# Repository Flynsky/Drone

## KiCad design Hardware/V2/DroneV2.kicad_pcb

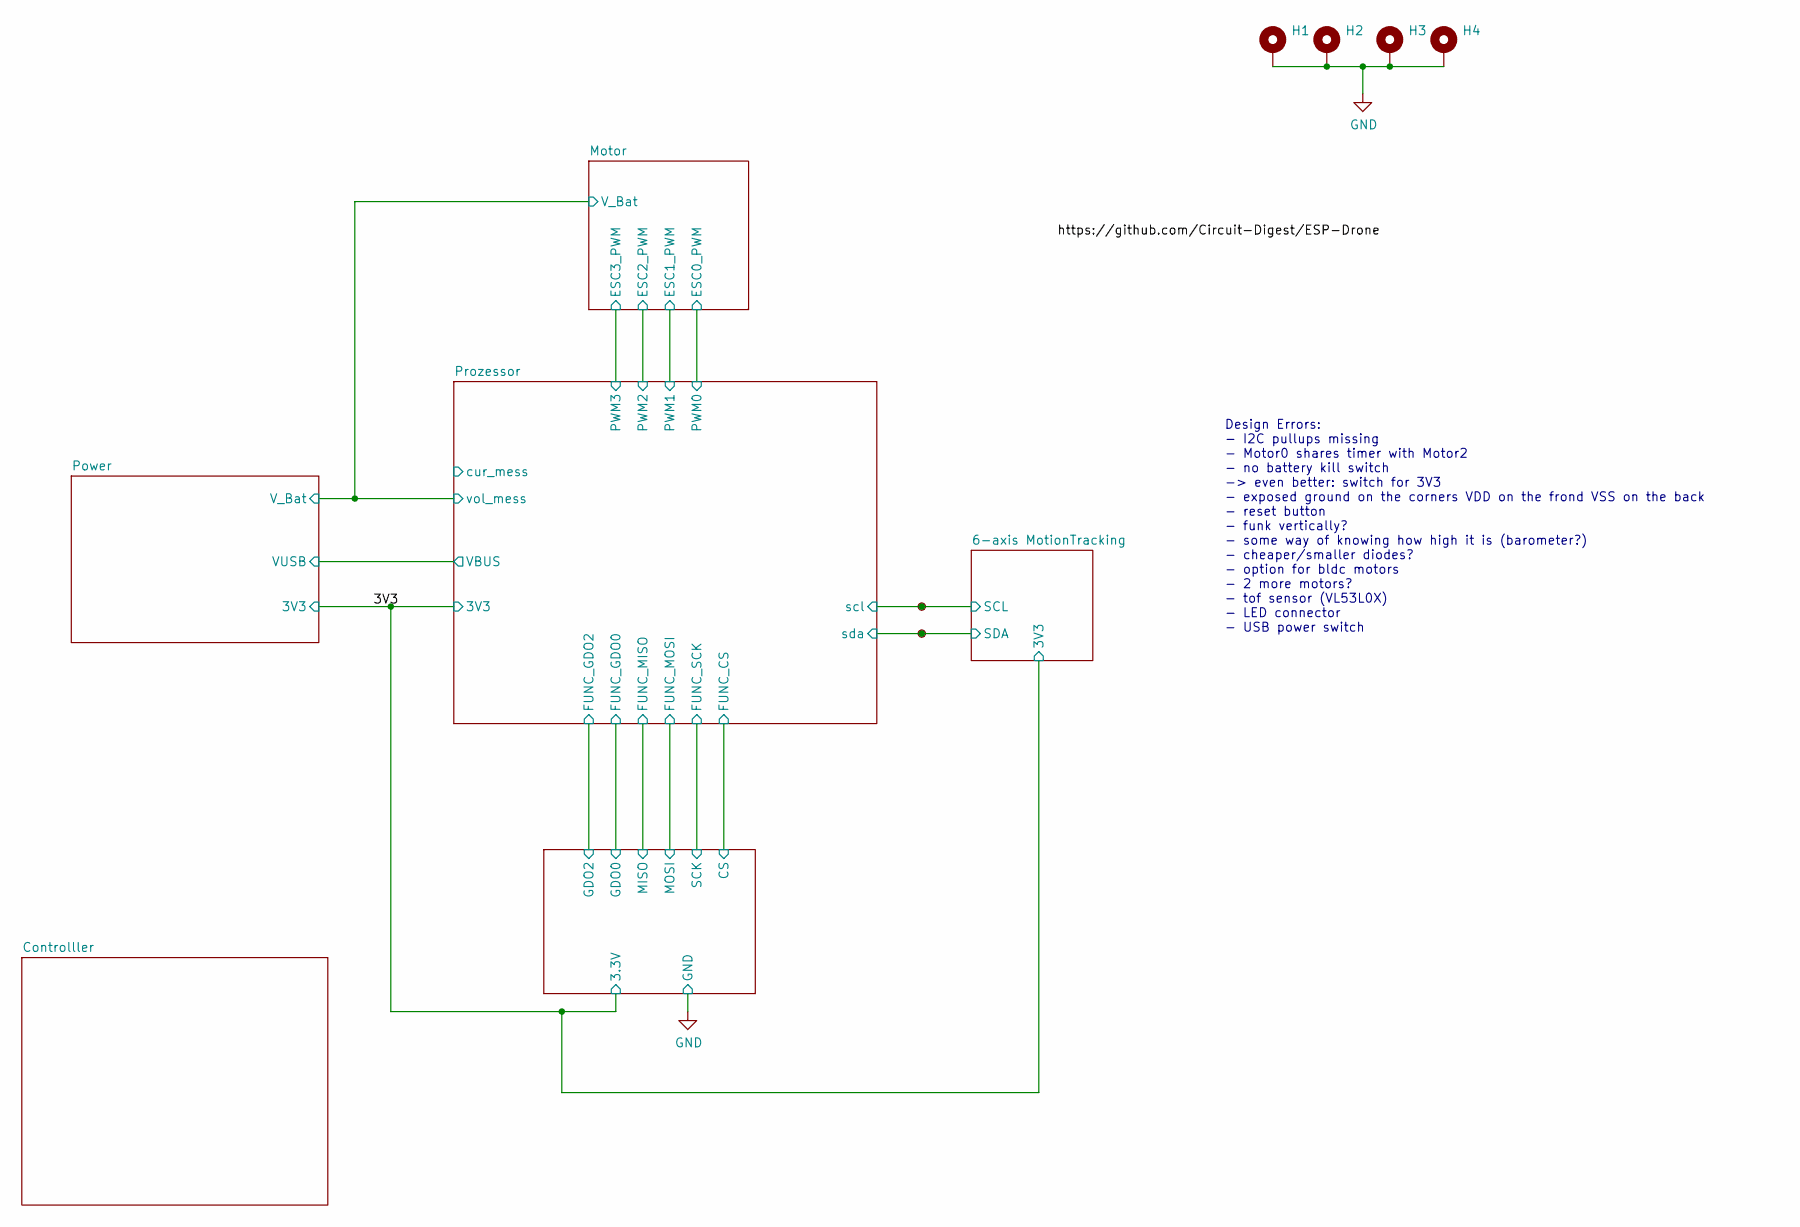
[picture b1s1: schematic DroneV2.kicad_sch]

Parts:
H1, H2, H3, H4: MountingHole_Pad; MountingHole_2.7mm_Pad_Via
TP1, TP2: TestPoint_Small; TestPoint_Pad_D1.0mm

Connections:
/6-axis MotionTracking/SCL: TP1.1; also elsewhere on the board
/6-axis MotionTracking/SDA: TP2.1; also elsewhere on the board
GND: H1.1, H2.1, H3.1, H4.1; also elsewhere on the board

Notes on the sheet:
Design Errors: - I2C pullups missing - Motor0 shares timer with Motor2 - no battery kill switch -> even better: switch for 3V3 - exposed ground on the corners VDD on the frond VSS on the back - reset button - funk vertically? - some way of knowing how high it is (barometer?) - cheaper/smaller diode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

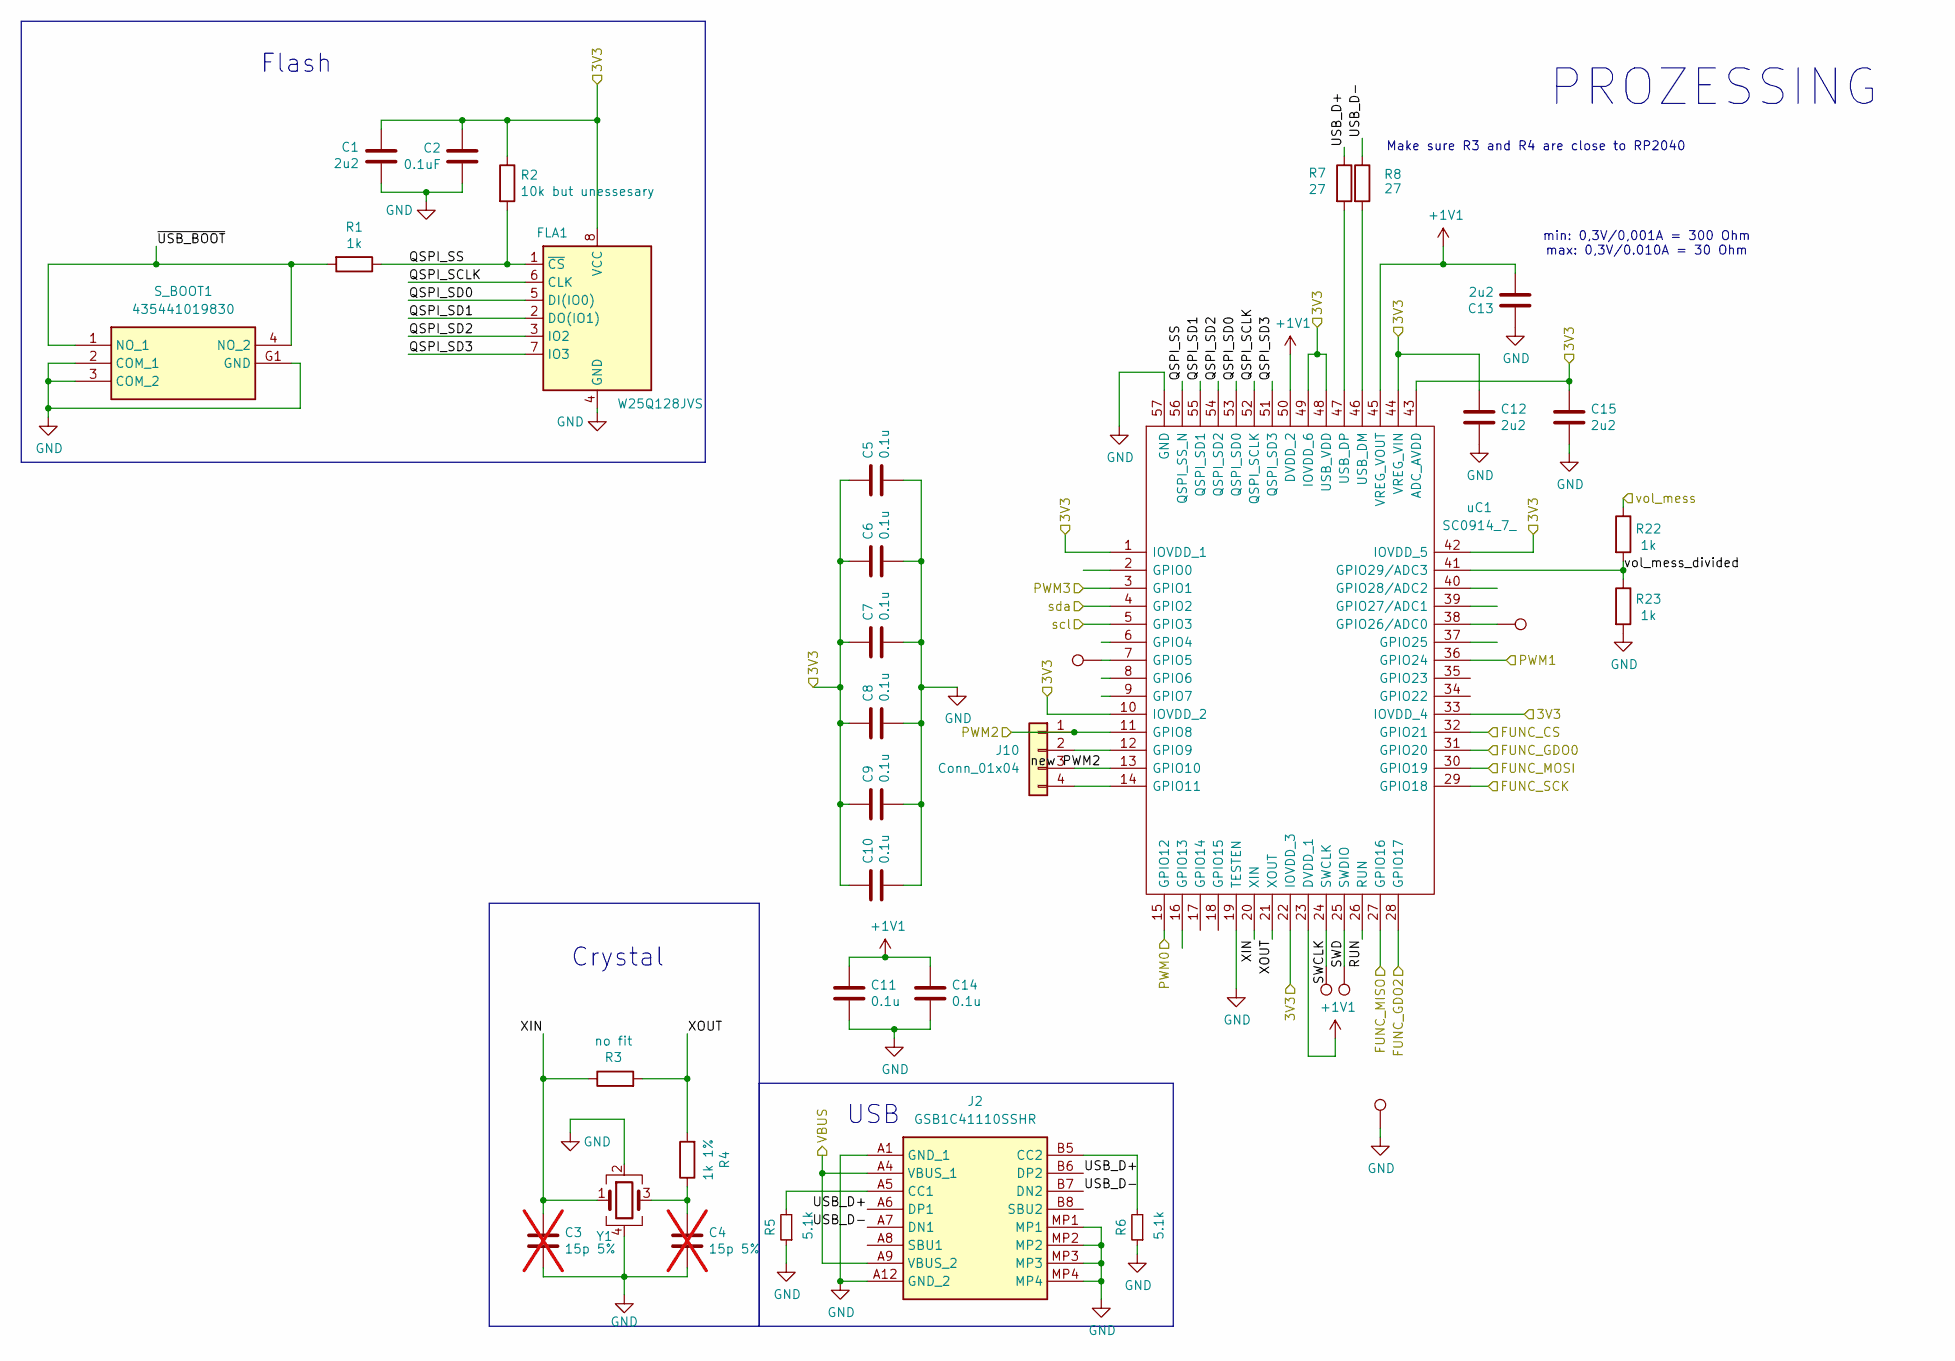
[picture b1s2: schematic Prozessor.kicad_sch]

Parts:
C1, C12, C13, C15: 2u2; C_0805_2012Metric_Pad1.18x1.45mm_HandSolder
C2: 0.1uF; C_0402_1005Metric_Pad0.74x0.62mm_HandSolder
C3, C4: 15p 5%; C_0402_1005Metric_Pad0.74x0.62mm_HandSolder; not fitted
C5, C6, C7, C8, C9, C10, C11, C14: 0.1u; C_0402_1005Metric_Pad0.74x0.62mm_HandSolder
FLA1: W25Q128JVS; SOIC127P790X216-8N
J2: GSB1C41110SSHR; Manufacturer_Part_Number GSB1C41110SSHR
J10: Conn_01x04; PinHeader_1x04_P1.00mm_Vertical_SMD_Pin1Left
R1, R22, R23: 1k; R_0603_1608Metric_Pad0.98x0.95mm_HandSolder
R2: 10k but unessesary; R_0603_1608Metric_Pad0.98x0.95mm_HandSolder
R3: no fit; R_0402_1005Metric_Pad0.72x0.64mm_HandSolder
R4: 1k 1%; R_0603_1608Metric_Pad0.98x0.95mm_HandSolder
R5, R6: 5.1k; R_0603_1608Metric_Pad0.98x0.95mm_HandSolder
R7, R8: 27; R_0603_1608Metric_Pad0.98x0.95mm_HandSolder
S_BOOT1: 435441019830; Mouser Part Number 710-435441019830
TP3, TP4, TP5, TP6, TP7: TestPoint; TestPoint_Pad_D1.0mm
Y1: ABM8G-12.000MHZ-4Y-T3; ABM8G; Mouser Part Number 815-ABM8G-12-4YT3
uC1: SC0914_7_; QFN40P700X700X90-57N-D; Mouser Part Number 358-SC09147

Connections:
+1V1: C11.1, C13.2, C14.1, uC1.23 (DVDD_1), uC1.45 (VREG_VOUT), uC1.50 (DVDD_2)
/3V3: C1.2, C2.1, C5.1, C6.1, C7.1, C8.1, C9.1, C10.1, C12.1, C15.1, FLA1.8 (VCC), R2.1, uC1.1 (IOVDD_1), uC1.10 (IOVDD_2), uC1.22 (IOVDD_3), uC1.33 (IOVDD_4), uC1.42 (IOVDD_5), uC1.43 (ADC_AVDD), uC1.44 (VREG_VIN), uC1.48 (USB_VDD), uC1.49 (IOVDD_6); also elsewhere on the board
/6-axis MotionTracking/SCL: uC1.5 (GPIO3); also elsewhere on the board
/6-axis MotionTracking/SDA: uC1.4 (GPIO2); also elsewhere on the board
/Funk/CS: uC1.32 (GPIO21); also elsewhere on the board
/Funk/GDO0: uC1.31 (GPIO20); also elsewhere on the board
/Funk/GDO2: uC1.28 (GPIO17); also elsewhere on the board
/Funk/MISO: uC1.27 (GPIO16); also elsewhere on the board
/Funk/MOSI: uC1.30 (GPIO19); also elsewhere on the board
/Funk/SCK: uC1.29 (GPIO18); also elsewhere on the board
/Motor/ESC0_PWM: uC1.15 (GPIO12); also elsewhere on the board
/Motor/ESC1_PWM: uC1.36 (GPIO24); also elsewhere on the board
/Motor/ESC2_PWM: J10.1, uC1.11 (GPIO8); also elsewhere on the board
/Motor/ESC3_PWM: uC1.3 (GPIO1); also elsewhere on the board
/Motor/V_Bat: R22.1; also elsewhere on the board
/Power/VUSB: J2.A4 (VBUS_1), J2.A9 (VBUS_2); also elsewhere on the board
/Prozessor/QSPI_SCLK: FLA1.6 (CLK), uC1.52 (QSPI_SCLK)
/Prozessor/QSPI_SD0: FLA1.5 (DI(IO0)), uC1.53 (QSPI_SD0)
/Prozessor/QSPI_SD1: FLA1.2 (DO(IO1)), uC1.55 (QSPI_SD1)
/Prozessor/QSPI_SD2: FLA1.3 (IO2), uC1.54 (QSPI_SD2)
/Prozessor/QSPI_SD3: FLA1.7 (IO3), uC1.51 (QSPI_SD3)
/Prozessor/QSPI_SS: FLA1.1 (~CS), R1.1, R2.2, uC1.56 (QSPI_SS_N)
/Prozessor/RUN: uC1.26 (RUN)
/Prozessor/SWCLK: TP3.1, uC1.24 (SWCLK)
/Prozessor/SWD: TP4.1, uC1.25 (SWDIO)
/Prozessor/USB_D+: J2.A6 (DP1), J2.B6 (DP2), R7.1
/Prozessor/USB_D-: J2.A7 (DN1), J2.B7 (DN2), R8.1
/Prozessor/XIN: C3.1, R3.1, Y1.1, uC1.20 (XIN)
/Prozessor/XOUT: R3.2, R4.2, uC1.21 (XOUT)
/Prozessor/new PWM2: J10.3, uC1.13 (GPIO10)
/Prozessor/vol_mess_divided: R22.2, R23.1, uC1.41 (GPIO29/ADC3)
/Prozessor/~USB_BOOT: R1.2, S_BOOT1.1 (NO_1), S_BOOT1.4 (NO_2)
GND: C1.1, C2.2, C3.2, C4.2, C5.2, C6.2, C7.2, C8.2, C9.2, C10.2, C11.2, C12.2, C13.1, C14.2, C15.2, FLA1.4 (GND), J2.A1 (GND_1), J2.A12 (GND_2), J2.MP1, J2.MP2, J2.MP3, J2.MP4, R5.1, R6.1, R23.2, S_BOOT1.2 (COM_1), S_BOOT1.3 (COM_2), S_BOOT1.G1 (GND), TP5.1, Y1.2, Y1.4, uC1.19 (TESTEN), uC1.57 (GND); also elsewhere on the board
unnamed: C4.1, R4.1, Y1.3
unnamed: J2.A5 (CC1), R5.2
unnamed: J2.B5 (CC2), R6.2
unnamed: J10.2, uC1.12 (GPIO9)
unnamed: J10.4, uC1.14 (GPIO11)
unnamed: TP7.1, uC1.7 (GPIO5)
unnamed: TP6.1, uC1.38 (GPIO26/ADC0)
unnamed: R8.2, uC1.46 (USB_DM)
unnamed: R7.2, uC1.47 (USB_DP)

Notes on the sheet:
Flash
min: 0,3V/0,001A = 300 Ohm max: 0,3V/0.010A = 30 Ohm
Crystal
PROZESSING
Make sure R3 and R4 are close to RP2040
USB

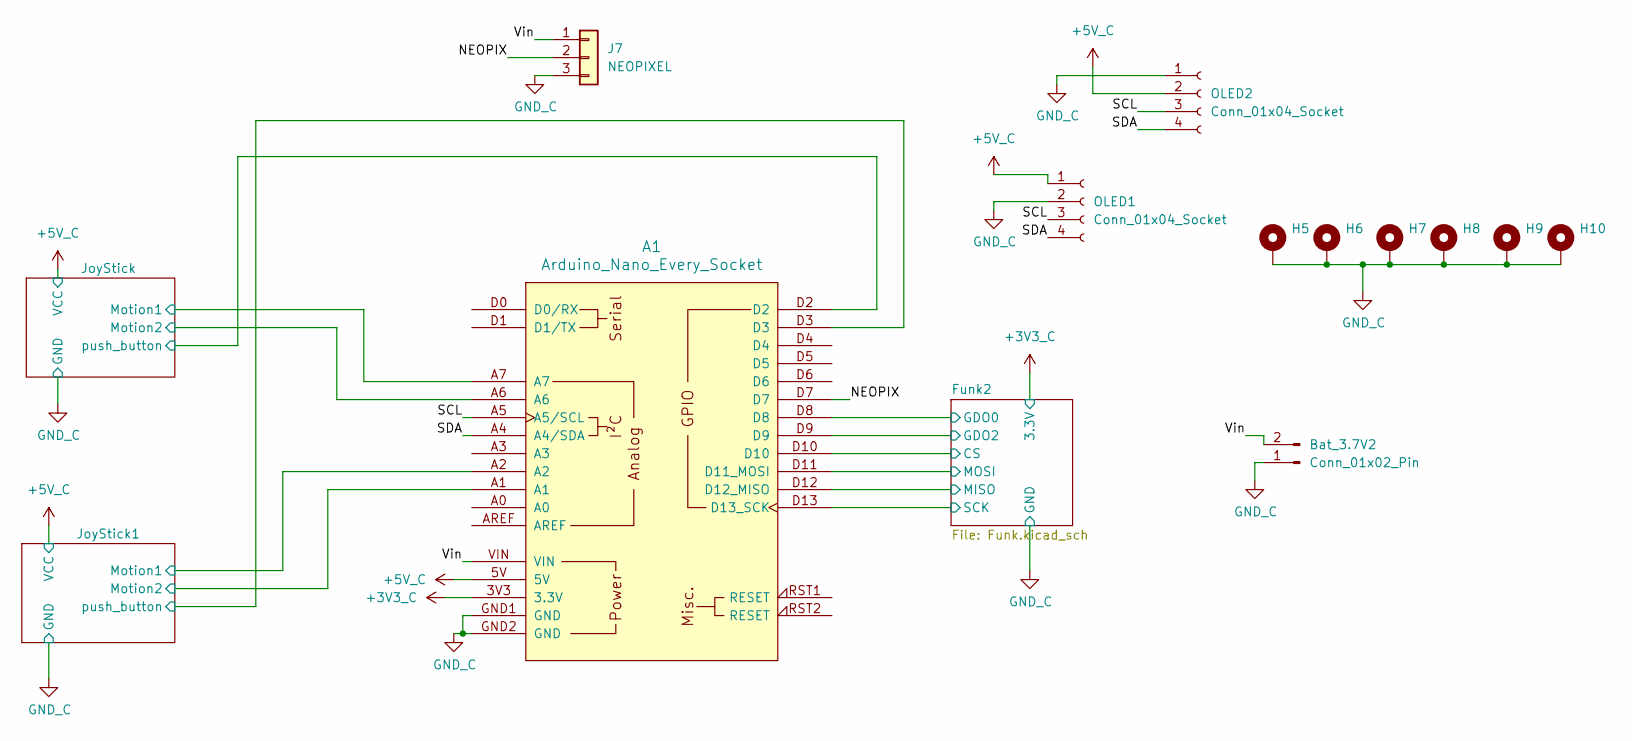
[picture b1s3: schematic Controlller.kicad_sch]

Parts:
A1: Arduino_Nano_Every_Socket
Bat_3.7V2: Conn_01x02_Pin; PinSocket_1x02_P2.54mm_Vertical
H5, H6, H7, H8, H9, H10: MountingHole_Pad; MountingHole_2.2mm_M2_DIN965_Pad
J7: NEOPIXEL; PinHeader_1x03_P2.54mm_Vertical
OLED1, OLED2: Conn_01x04_Socket; PinHeader_1x04_P2.54mm_Vertical

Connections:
+5V_C: A1.5V, OLED1.1, OLED2.2; also elsewhere on the board
/Controlller/NEOPIX: A1.D7, J7.2
/Controlller/SCL: A1.A5 (A5/SCL), OLED1.3, OLED2.3
/Controlller/SDA: A1.A4 (A4/SDA), OLED1.4, OLED2.4
/Controlller/Vin: A1.VIN, Bat_3.7V2.2, J7.1
GND_C: A1.GND1 (GND), A1.GND2 (GND), Bat_3.7V2.1, H5.1, H6.1, H7.1, H8.1, H9.1, H10.1, J7.3, OLED1.2, OLED2.1; also elsewhere on the board

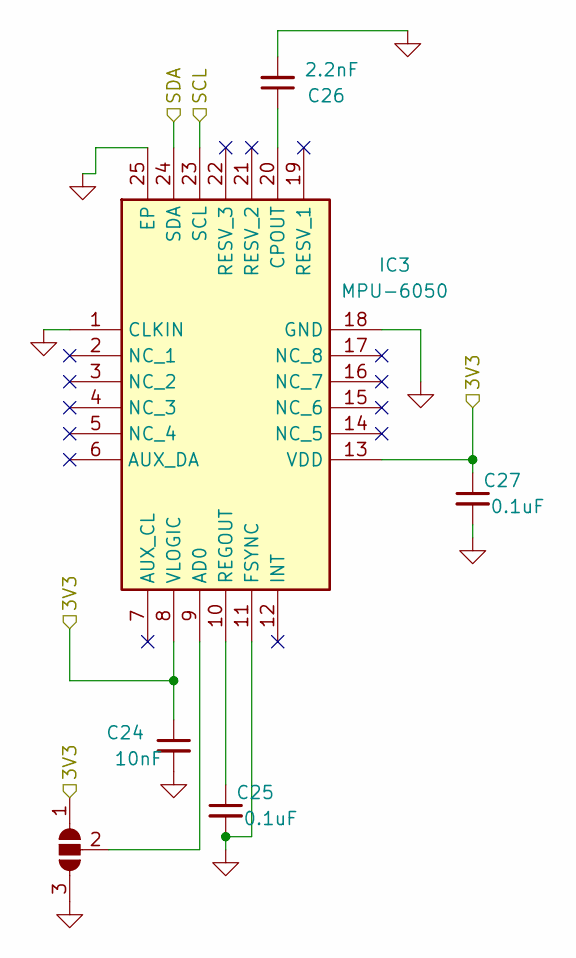
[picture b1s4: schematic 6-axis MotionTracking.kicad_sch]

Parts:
C24: 10nF; C_0402_1005Metric
C25, C27: 0.1uF; C_0402_1005Metric
C26: 2.2nF; C_0402_1005Metric
IC3: MPU-6050; MPU6050; Mouser Part Number 410-MPU-6050
JP1: SolderJumper_3_Open; SolderJumper-3_P1.3mm_Open_RoundedPad1.0x1.5mm_NumberLabels

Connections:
/3V3: C24.1, C27.1, IC3.8 (VLOGIC), IC3.13 (VDD), JP1.1 (A); also elsewhere on the board
/6-axis MotionTracking/SCL: IC3.23 (SCL); also elsewhere on the board
/6-axis MotionTracking/SDA: IC3.24 (SDA); also elsewhere on the board
GND: C24.2, C25.2, C26.2, C27.2, IC3.1 (CLKIN), IC3.11 (FSYNC), IC3.18 (GND), IC3.25 (EP), JP1.3 (B); also elsewhere on the board
unnamed: IC3.9 (AD0), JP1.2 (C)
unnamed: C26.1, IC3.20 (CPOUT)
unnamed: C25.1, IC3.10 (REGOUT)

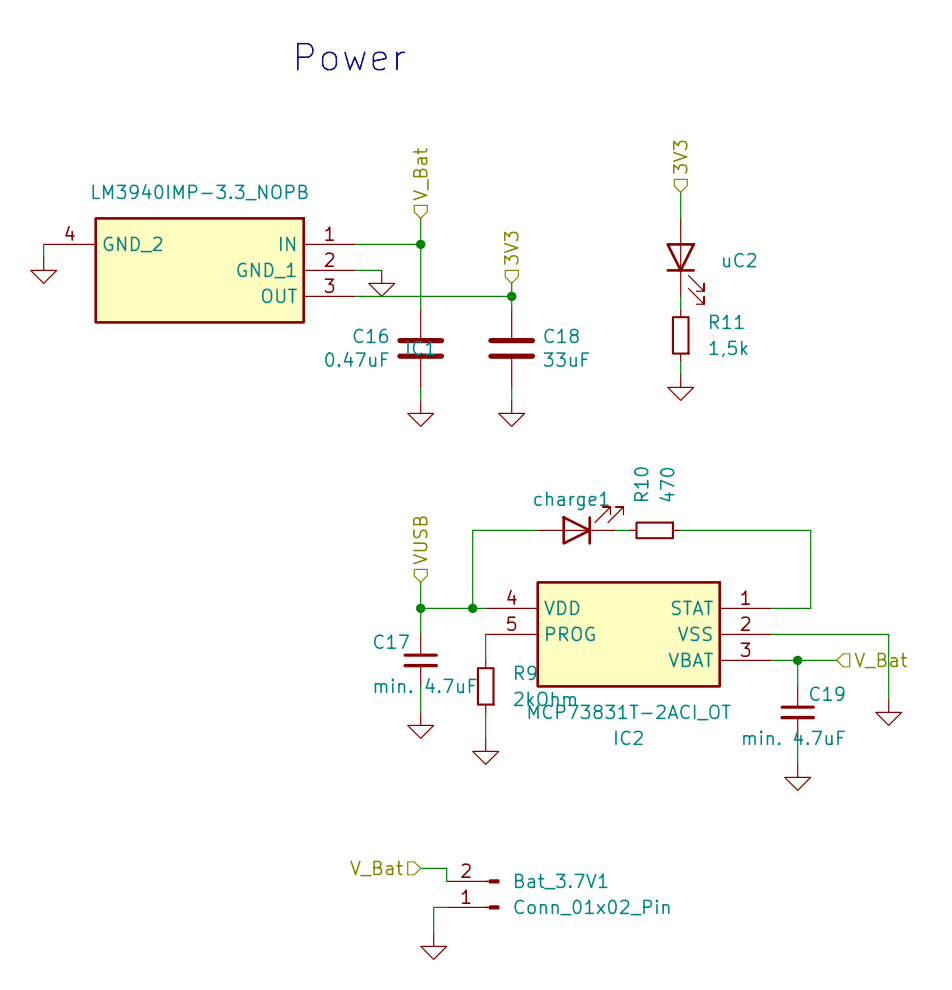
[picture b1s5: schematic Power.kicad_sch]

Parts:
Bat_3.7V1: Conn_01x02_Pin; PinSocket_1x02_P2.54mm_Vertical
C16: 0.47uF; C_0805_2012Metric
C17, C19: min. 4.7uF; C_0805_2012Metric
C18: 33uF; C_0805_2012Metric
IC1: LM3940IMP-3.3_NOPB; SOT230P700X180-4N; Mouser Part Number 926-LM3940IMP3.3NOPB
IC2: MCP73831T-2ACI_OT; SOT95P270X145-5N; Mouser Part Number 579-MCP73831T-2ACIOT
R9: 2kOhm; R_0603_1608Metric_Pad0.98x0.95mm_HandSolder
R10: 470; R_0603_1608Metric_Pad0.98x0.95mm_HandSolder
R11: 1,5k; R_0603_1608Metric_Pad0.98x0.95mm_HandSolder
charge1: APTD2012LCGCK; LEDC2012X120N; Mouser Part Number 604-APTD2012LCGCK
uC2: APTD2012LCGCK; LEDC2012X120N; Mouser Part Number 604-APTD2012LCGCK

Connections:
/3V3: C18.1, IC1.3 (OUT), uC2.2 (A); also elsewhere on the board
/Motor/V_Bat: Bat_3.7V1.2, C16.1, C19.1, IC1.1 (IN), IC2.3 (VBAT); also elsewhere on the board
/Power/VUSB: C17.1, IC2.4 (VDD), charge1.2 (A); also elsewhere on the board
GND: Bat_3.7V1.1, C16.2, C17.2, C18.2, C19.2, IC1.2 (GND_1), IC1.4 (GND_2), IC2.2 (VSS), R9.1, R11.1; also elsewhere on the board
unnamed: IC2.5 (PROG), R9.2
unnamed: IC2.1 (STAT), R10.1
unnamed: R10.2, charge1.1 (K)
unnamed: R11.2, uC2.1 (K)

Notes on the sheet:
Power

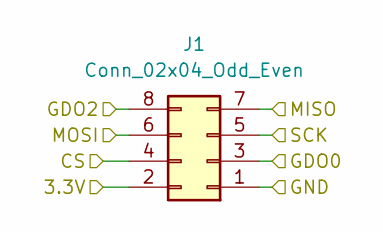
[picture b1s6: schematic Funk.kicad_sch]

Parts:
J1: Conn_02x04_Odd_Even; PinHeader_2x04_P2.54mm_Vertical

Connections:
/3V3: J1.2; also elsewhere on the board
/Funk/CS: J1.4; also elsewhere on the board
/Funk/GDO0: J1.3; also elsewhere on the board
/Funk/GDO2: J1.8; also elsewhere on the board
/Funk/MISO: J1.7; also elsewhere on the board
/Funk/MOSI: J1.6; also elsewhere on the board
/Funk/SCK: J1.5; also elsewhere on the board
GND: J1.1; also elsewhere on the board

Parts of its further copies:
J8: Conn_02x04_Odd_Even; PinHeader_2x04_P2.54mm_Vertical

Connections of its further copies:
+3V3_C: J8.2
/Controlller/Funk2/CS: J8.4
/Controlller/Funk2/GDO0: J8.3
/Controlller/Funk2/GDO2: J8.8
/Controlller/Funk2/MISO: J8.7
/Controlller/Funk2/MOSI: J8.6
/Controlller/Funk2/SCK: J8.5
GND_C: J8.1; also elsewhere on the board

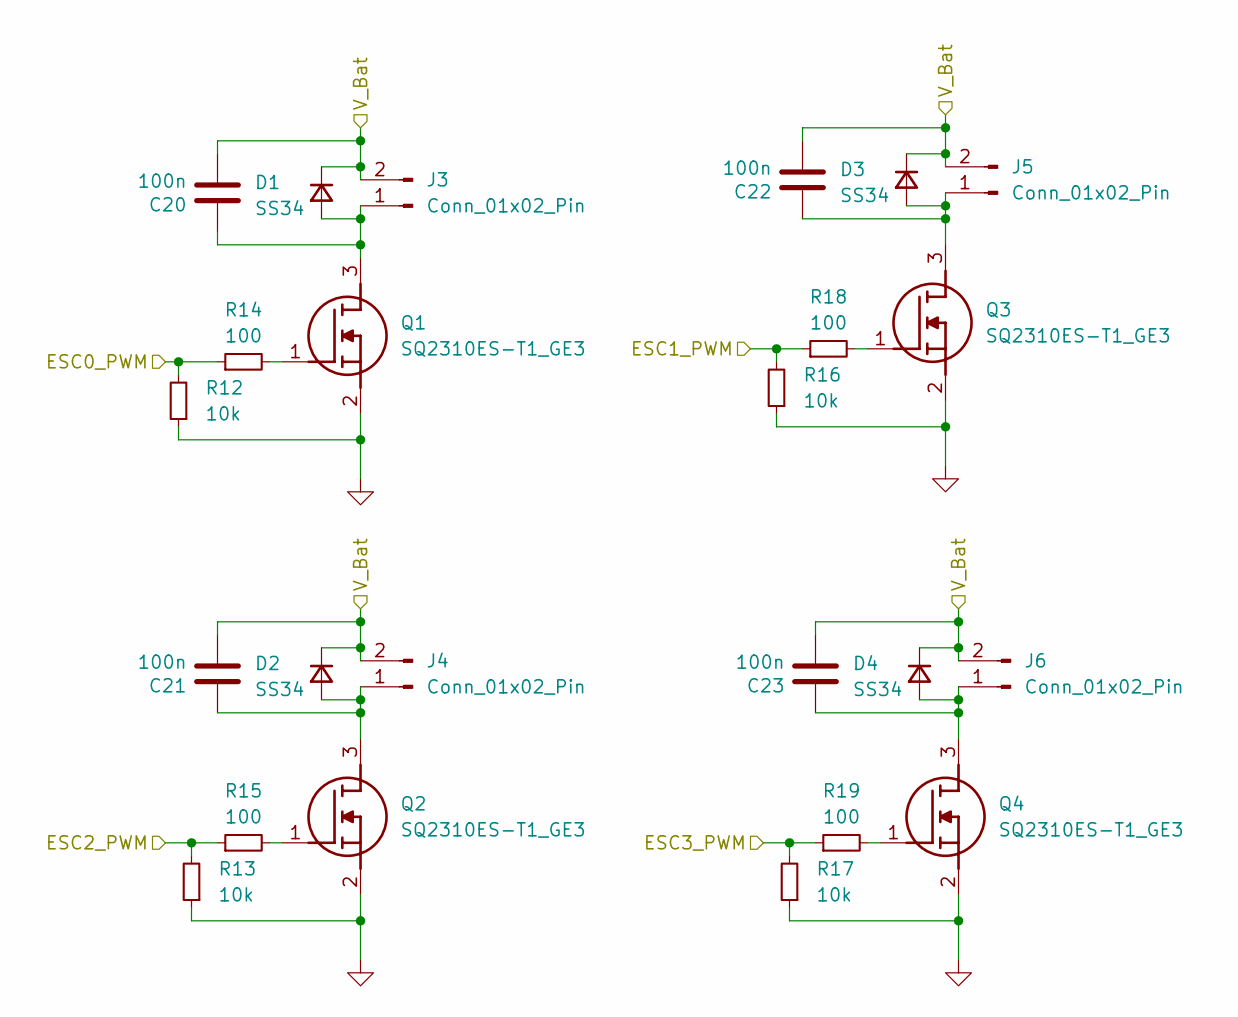
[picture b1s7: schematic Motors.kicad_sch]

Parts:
C20, C21, C22, C23: 100n; C_0402_1005Metric
D1, D2, D3, D4: SS34; DIOM8059X256N; Mouser Part Number 821-SS34
J3, J4, J5, J6: Conn_01x02_Pin; PinSocket_1x02_P2.54mm_Vertical
Q1, Q2, Q3, Q4: SQ2310ES-T1_GE3; SOT95P237X112-3N; Mouser Part Number 78-SQ2310ES-T1_GE3
R12, R13, R16, R17: 10k; R_0603_1608Metric_Pad0.98x0.95mm_HandSolder
R14, R15, R18, R19: 100; R_0603_1608Metric_Pad0.98x0.95mm_HandSolder

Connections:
/Motor/ESC0_PWM: R12.2, R14.1; also elsewhere on the board
/Motor/ESC1_PWM: R16.2, R18.1; also elsewhere on the board
/Motor/ESC2_PWM: R13.2, R15.1; also elsewhere on the board
/Motor/ESC3_PWM: R17.2, R19.1; also elsewhere on the board
/Motor/V_Bat: C20.2, C21.2, C22.2, C23.2, D1.1 (K), D2.1 (K), D3.1 (K), D4.1 (K), J3.2, J4.2, J5.2, J6.2; also elsewhere on the board
GND: Q1.2 (S), Q2.2 (S), Q3.2 (S), Q4.2 (S), R12.1, R13.1, R16.1, R17.1; also elsewhere on the board
unnamed: C20.1, D1.2 (A), J3.1, Q1.3 (D)
unnamed: C21.1, D2.2 (A), J4.1, Q2.3 (D)
unnamed: C22.1, D3.2 (A), J5.1, Q3.3 (D)
unnamed: C23.1, D4.2 (A), J6.1, Q4.3 (D)
unnamed: Q1.1 (G), R14.2
unnamed: Q2.1 (G), R15.2
unnamed: Q3.1 (G), R18.2
unnamed: Q4.1 (G), R19.2

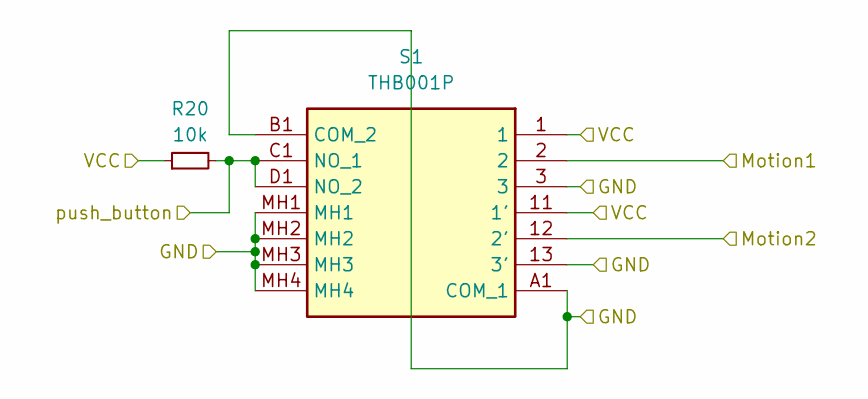
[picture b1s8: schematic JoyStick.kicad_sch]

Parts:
R20: 10k; R_0603_1608Metric_Pad0.98x0.95mm_HandSolder
S1: THB001P; Mouser Part Number 611-THB001P

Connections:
+5V_C: R20.1, S1.1, S1.11 (1'); also elsewhere on the board
/Controlller/JoyStick/Motion1: S1.2
/Controlller/JoyStick/Motion2: S1.12 (2')
/Controlller/JoyStick/push_button: R20.2, S1.C1 (NO_1), S1.D1 (NO_2)
GND_C: S1.3, S1.13 (3'), S1.A1 (COM_1), S1.B1 (COM_2), S1.MH1, S1.MH2, S1.MH3, S1.MH4; also elsewhere on the board

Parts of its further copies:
R21: 10k; R_0603_1608Metric_Pad0.98x0.95mm_HandSolder
S2: THB001P; Mouser Part Number 611-THB001P

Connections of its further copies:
+5V_C: R21.1, S2.1, S2.11 (1'); also elsewhere on the board
/Controlller/JoyStick1/Motion1: S2.2
/Controlller/JoyStick1/Motion2: S2.12 (2')
/Controlller/JoyStick1/push_button: R21.2, S2.C1 (NO_1), S2.D1 (NO_2)
GND_C: S2.3, S2.13 (3'), S2.A1 (COM_1), S2.B1 (COM_2), S2.MH1, S2.MH2, S2.MH3, S2.MH4; also elsewhere on the board

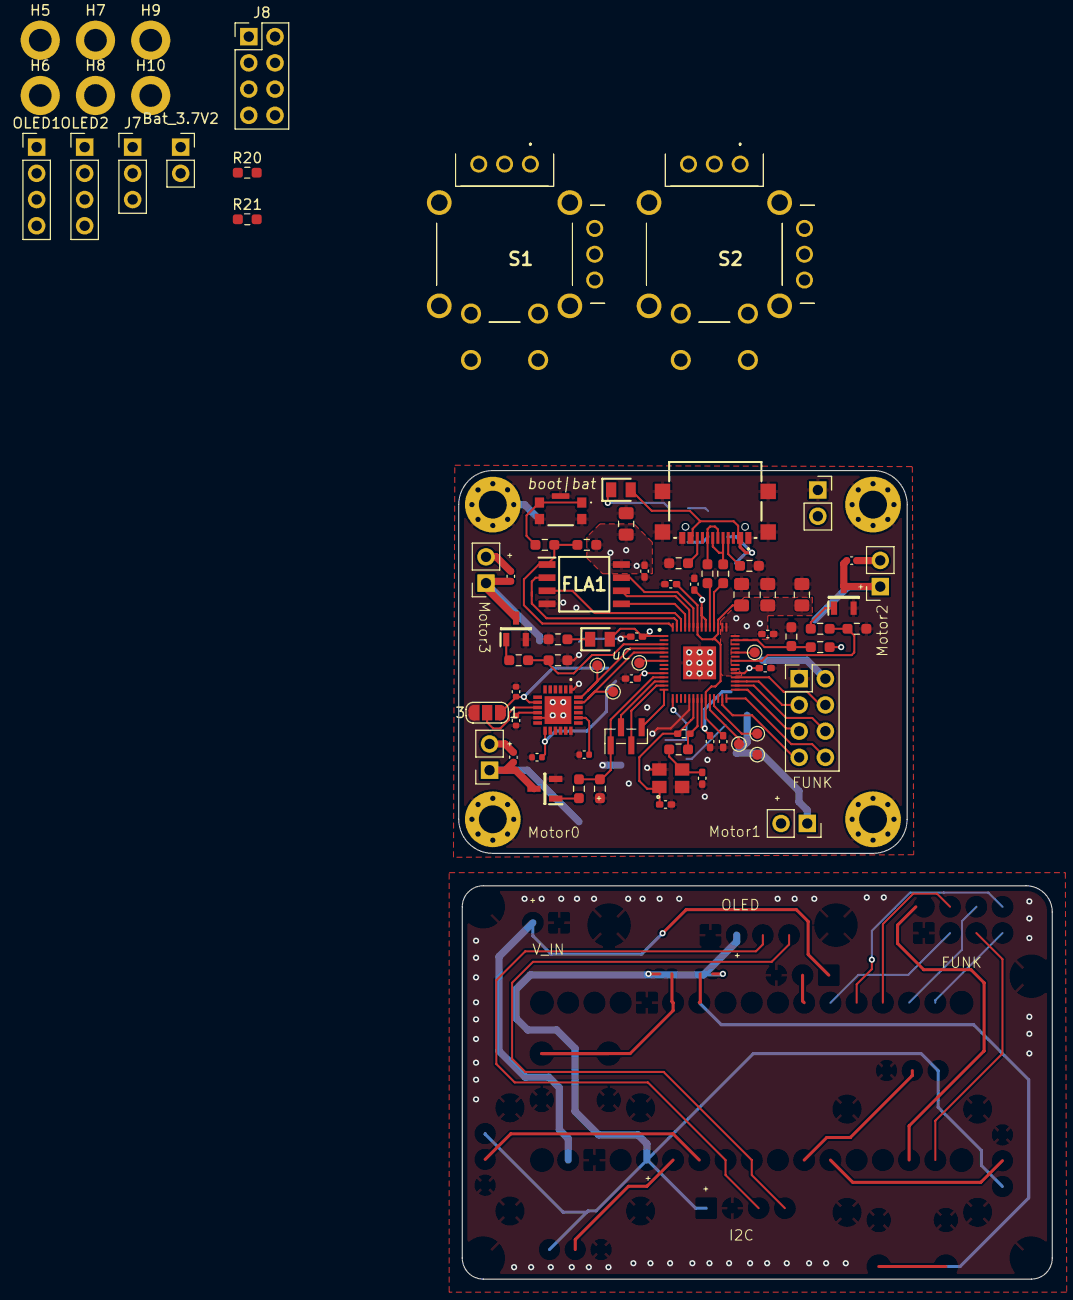
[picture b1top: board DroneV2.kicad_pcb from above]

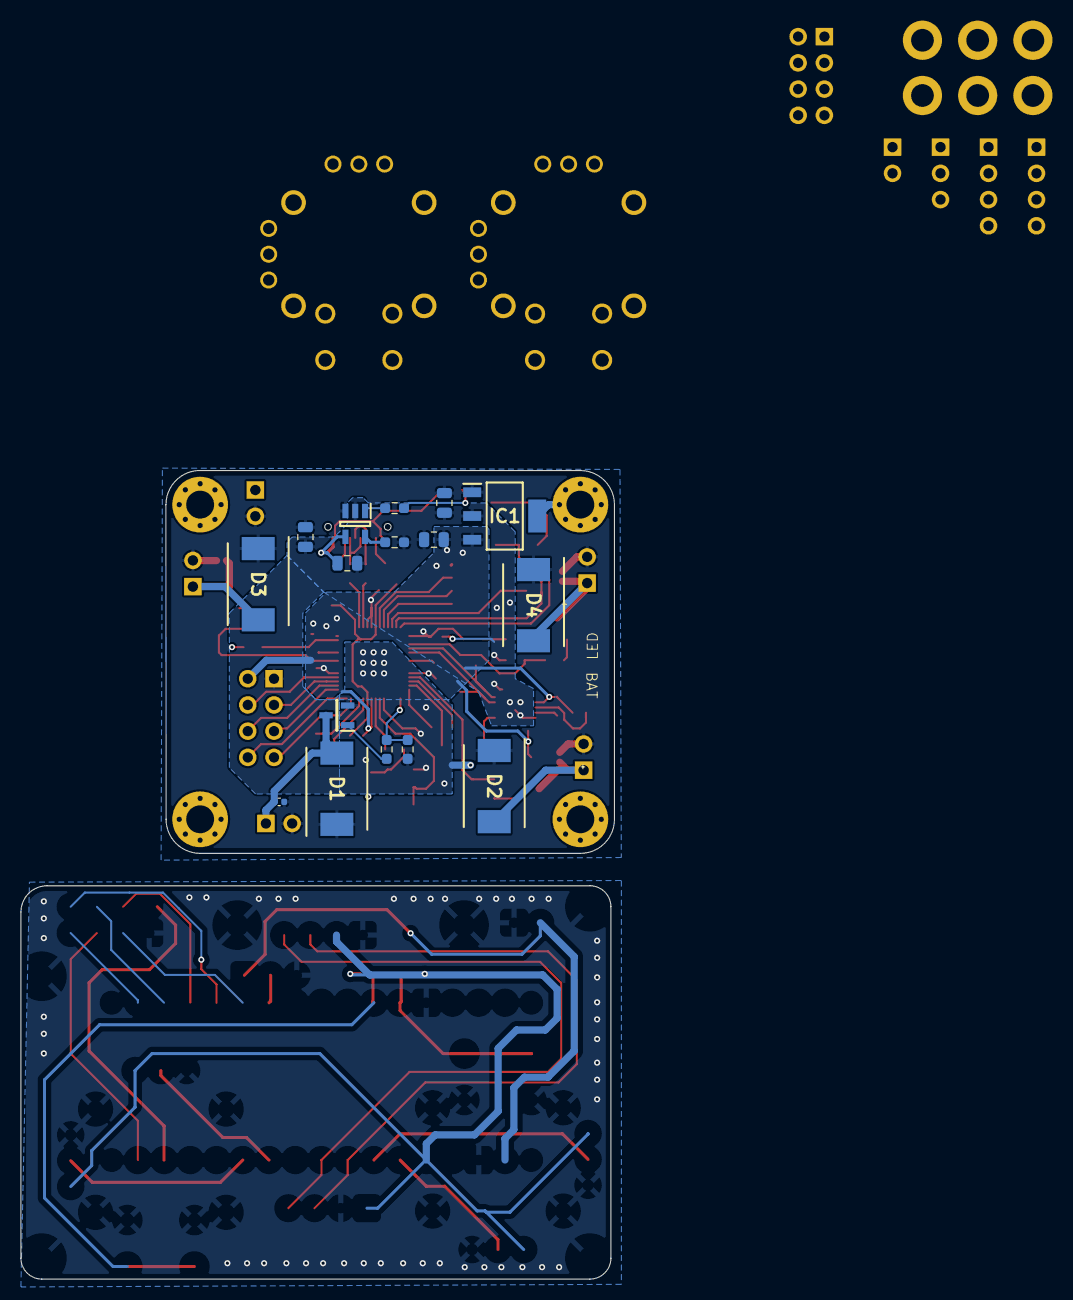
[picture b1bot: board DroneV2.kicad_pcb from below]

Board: 2 copper layers, 43.4 x 37.1 mm, 100 parts (16 on the bottom side), 63 nets.

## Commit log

2024-06-16 pushing current status
2024-06-20 adjusted frequency
2024-06-21 updates pid
2024-06-21 boosted pid controller
2024-10-19 added current version
2024-10-19 added photos
